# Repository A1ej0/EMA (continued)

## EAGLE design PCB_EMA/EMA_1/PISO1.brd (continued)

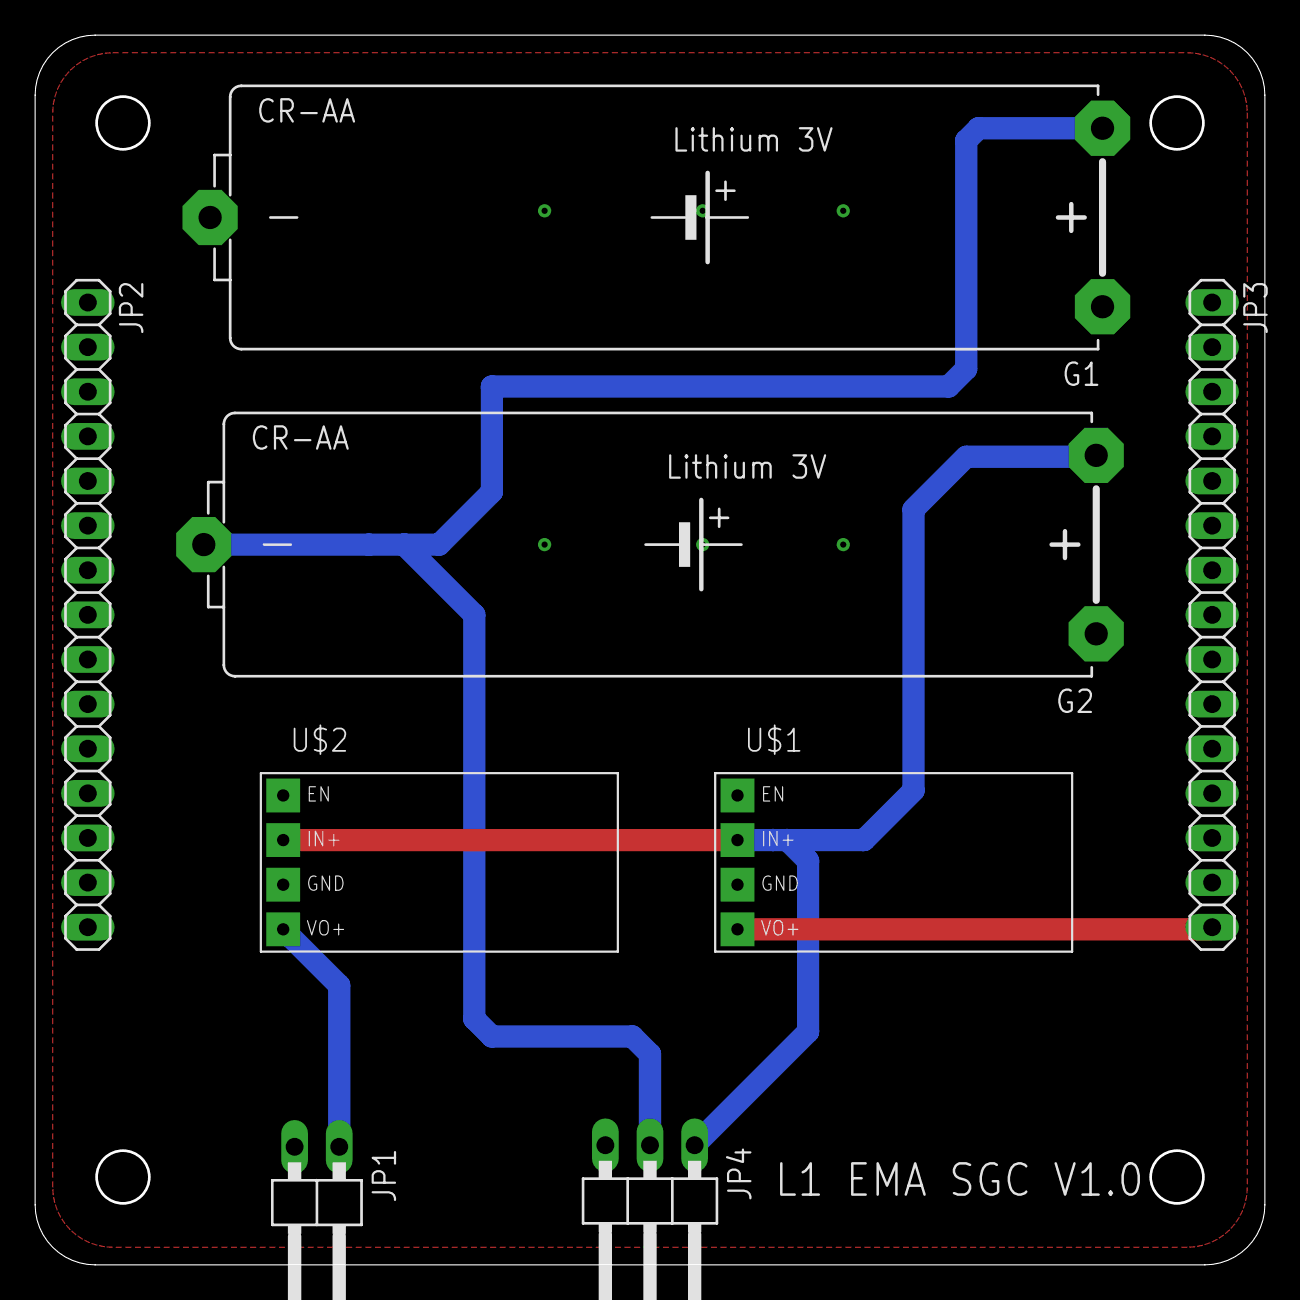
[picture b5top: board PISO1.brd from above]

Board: 2 copper layers, 70.0 x 70.0 mm, 8 parts (0 on the bottom side), 5 nets.

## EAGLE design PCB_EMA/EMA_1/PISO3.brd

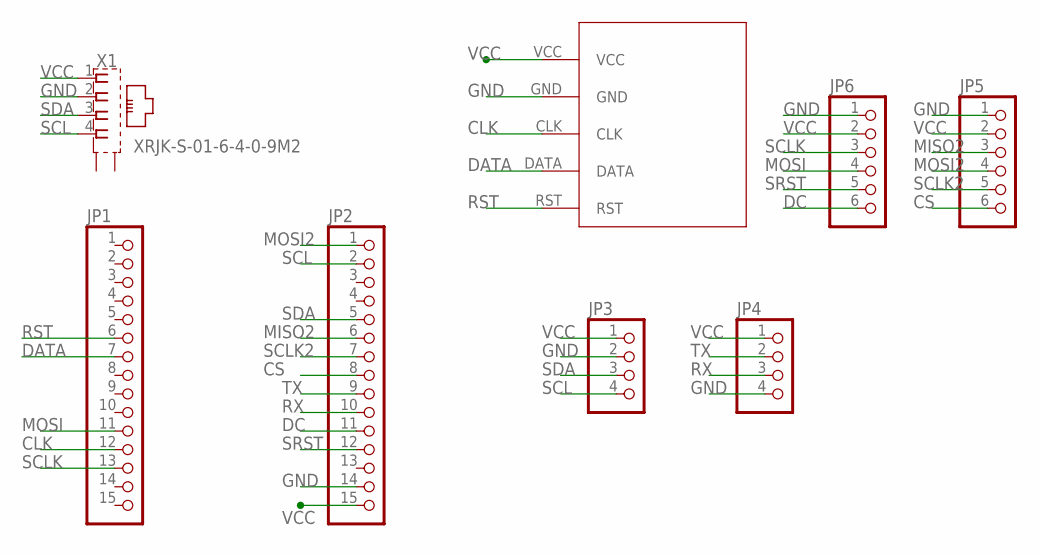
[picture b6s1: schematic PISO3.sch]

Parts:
JP1, JP2: PINHD-1X15; 1X15
JP3, JP4: PINHD-1X4; 1X04
JP5, JP6: PINHD-1X6; 1X06
U$1: DS1302_MODULE; DS1307_MODULE
X1: XRJK-S-01-6-4-0-9M2

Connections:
CLK: JP1.12, U$1.CLK
CS: JP2.8, JP5.6
DATA: JP1.7, U$1.DATA
DC: JP2.11, JP6.6
GND: JP2.14, JP3.2, JP4.4, JP5.1, JP6.1, U$1.GND, X1.2
MISO2: JP2.6, JP5.3
MOSI: JP1.11, JP6.4
MOSI2: JP2.1, JP5.4
RST: JP1.6, U$1.RST
RX: JP2.10, JP4.3
SCL: JP2.2, JP3.4, X1.4
SCLK: JP1.13, JP6.3
SCLK2: JP2.7, JP5.5
SDA: JP2.5, JP3.3, X1.3
SRST: JP2.12, JP6.5
TX: JP2.9, JP4.2
VCC: JP2.15, JP3.1, JP4.1, JP5.2, JP6.2, U$1.VCC, X1.1

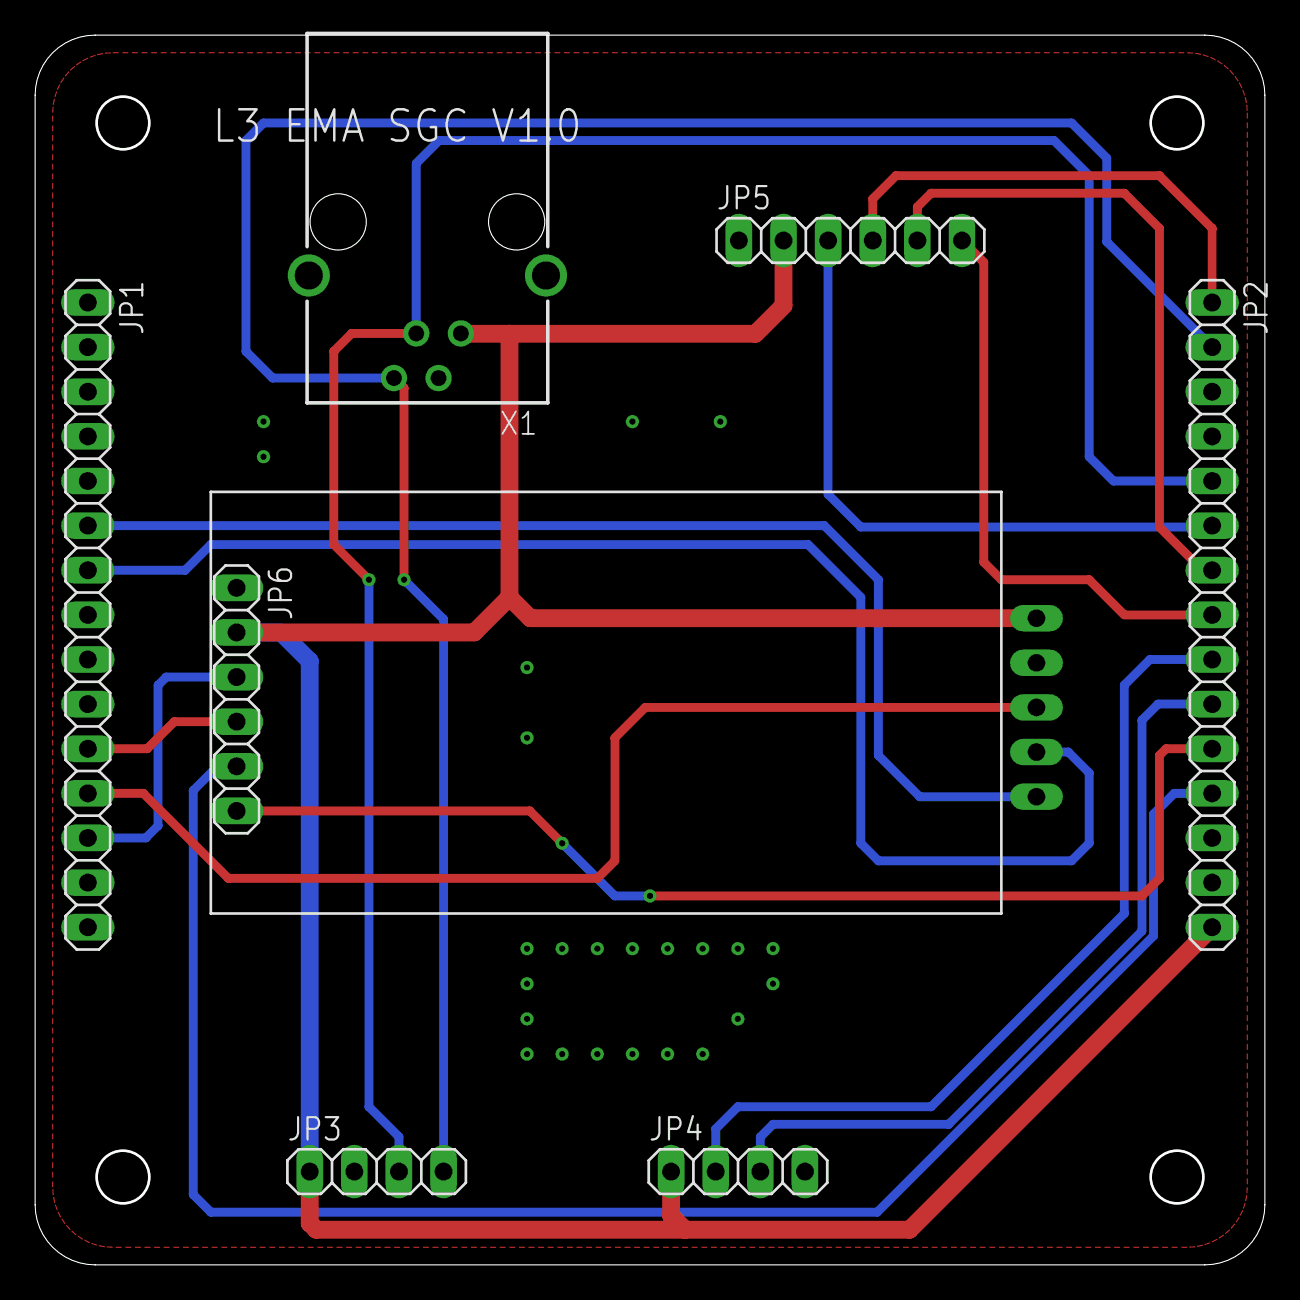
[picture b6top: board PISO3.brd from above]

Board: 2 copper layers, 70.0 x 70.0 mm, 8 parts (1 on the bottom side), 17 nets.

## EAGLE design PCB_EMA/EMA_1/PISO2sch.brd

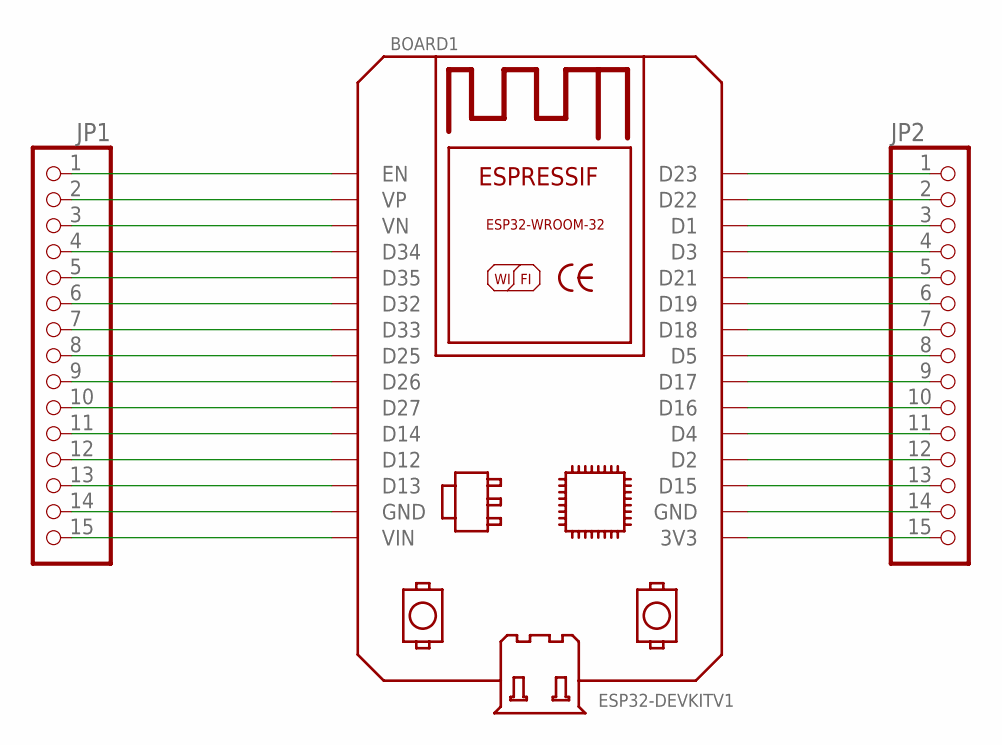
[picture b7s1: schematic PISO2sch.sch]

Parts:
BOARD1: ESP32DEVKITV1; ESP32-DEVKITV1
JP1, JP2: PINHD-1X15; 1X15

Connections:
unnamed: BOARD1.D34, JP1.4
unnamed: BOARD1.VN, JP1.3
unnamed: BOARD1.VP, JP1.2
unnamed: BOARD1.EN, JP1.1
unnamed: BOARD1.D35, JP1.5
unnamed: BOARD1.D32, JP1.6
unnamed: BOARD1.D33, JP1.7
unnamed: BOARD1.D25, JP1.8
unnamed: BOARD1.D26, JP1.9
unnamed: BOARD1.D27, JP1.10
unnamed: BOARD1.D14, JP1.11
unnamed: BOARD1.D12, JP1.12
unnamed: BOARD1.D13, JP1.13
unnamed: BOARD1.GND, JP1.14
unnamed: BOARD1.VIN, JP1.15
unnamed: BOARD1.D23, JP2.1
unnamed: BOARD1.D22, JP2.2
unnamed: BOARD1.D1, JP2.3
unnamed: BOARD1.D3, JP2.4
unnamed: BOARD1.D21, JP2.5
unnamed: BOARD1.D19, JP2.6
unnamed: BOARD1.D18, JP2.7
unnamed: BOARD1.D5, JP2.8
unnamed: BOARD1.D17, JP2.9
unnamed: BOARD1.D16, JP2.10
unnamed: BOARD1.D4, JP2.11
unnamed: BOARD1.D2, JP2.12
unnamed: BOARD1.D15, JP2.13
unnamed: BOARD1.GND@1 (GND), JP2.14
unnamed: BOARD1.3V3, JP2.15

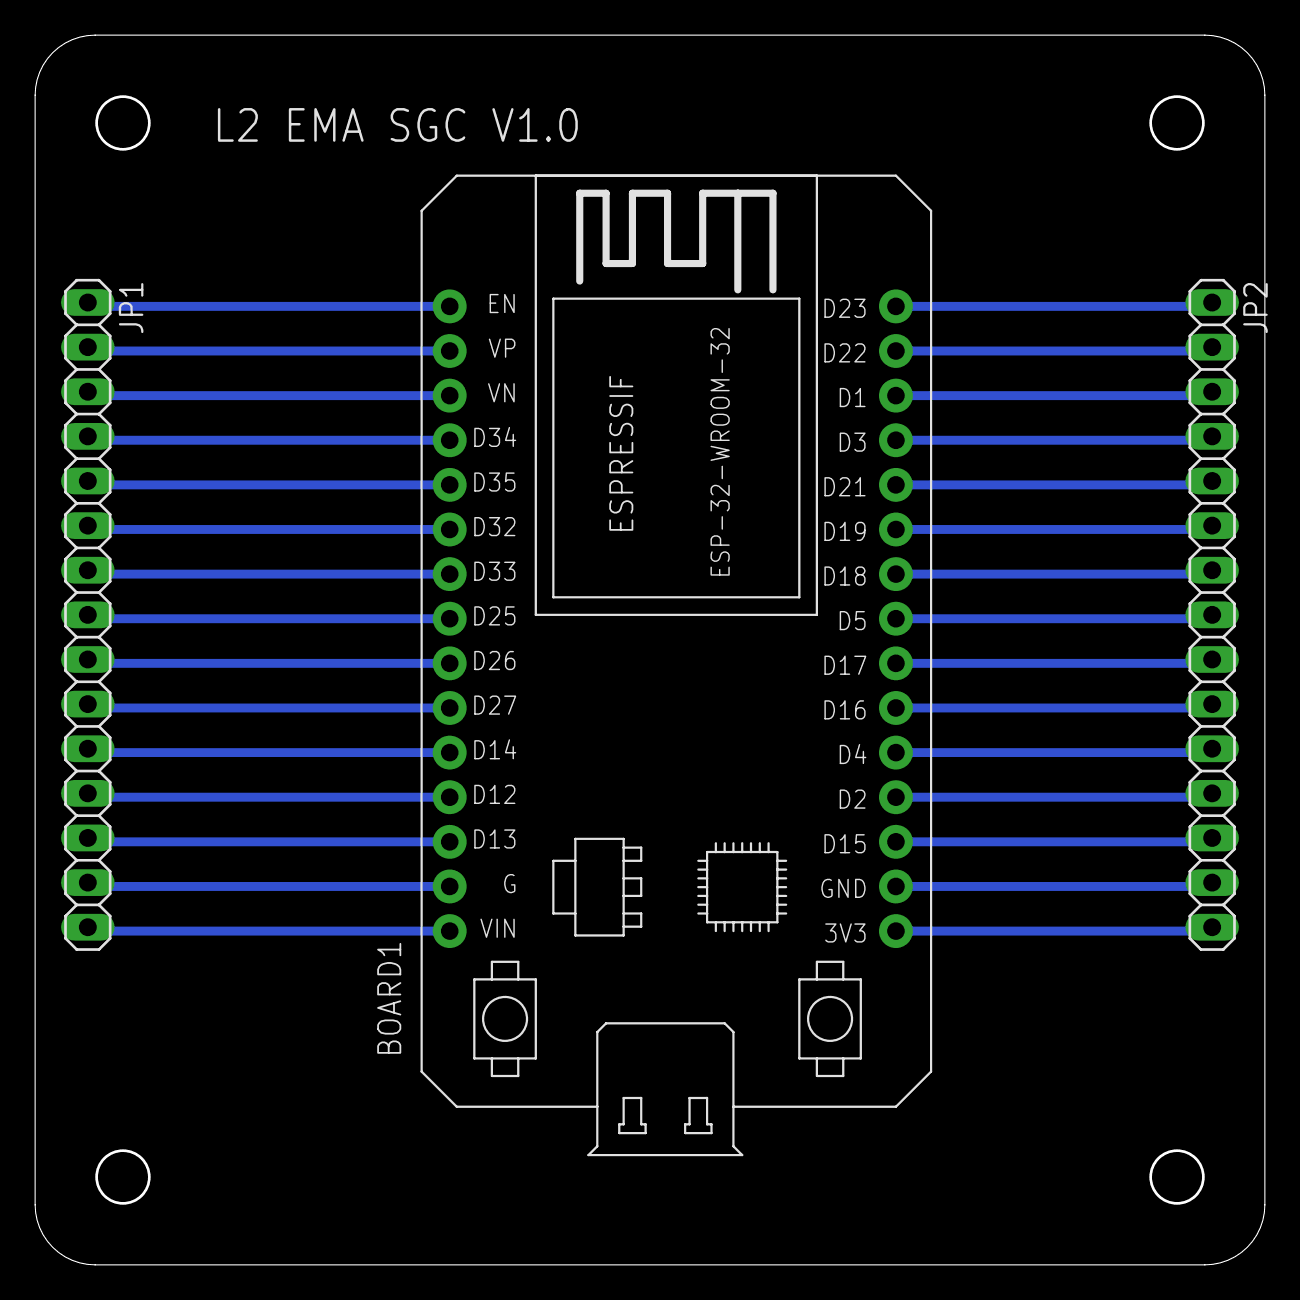
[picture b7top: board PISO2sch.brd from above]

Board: 2 copper layers, 70.0 x 70.0 mm, 3 parts (0 on the bottom side), 30 nets.

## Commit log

2023-02-27 Librerias
2023-02-27 Libreria Global EMA
2023-02-27 Hoja principal del proyecto
2023-03-01 Bluetooth low energy and mpu sensor
2023-03-01 aplicación test BLE y extensión requerida
2023-03-02 EMA_2 updated
2023-03-03 menu local, completo, falta integrar.
2023-03-03 modulo GSM, ajustes y consideraciones iniciales
2023-03-03 menu integrado a EMA, funcionalidad ok
2023-03-03 Etapas del proceso agregadas
2023-03-03 Etapas del proceso UPDATE
2023-03-13 added node-red flows
2023-03-13 corrected node-red flows
2023-03-13 Aplicacion para generar ema.conf
2023-03-13 App para generar conf, version python
2023-03-13 libreria actualizada
    agregado OLED,
    eliminado LCD,
    agregado acelerometro y magnetometro
2023-03-13 Actualizacion menu
    deteccion de sd y archivo de config en la SD
2023-03-13 eliminacion de LCD
    se reemplaza por OLED
2023-03-13 Actualizacion con encoder
2023-03-14 ajustes generales, sensor hall y excepciones
2023-04-10 Create EMA_v20.py
    Libreria optimizada.
2023-04-10 Create main_V2.0.py
    Version optimizada del codigo, control desde archivo local.
2023-04-11 Update EMA_v20.py
    Version revisada, añadido RTC
2023-04-11 Update main_V2.0.py
    Version revisada, añadido RTC
2023-05-13 Esquematico
2023-05-15 PCB design added
2023-05-24 added app bluetooth ver 2
2023-05-26 Create EMA_AlertaGSM.ino
    Modulo GSM de alerta externo
2023-06-06 Actualizacion EMA
    Ultimos avances propuestos
2023-06-06 BLE actualizado
    Actualizacion, para reemplazar valores reales
2023-06-06 ultima version 6 jun
2023-06-13 added app
2023-06-14 Actualizacion EMA
2023-06-15 edited
2023-06-16 app actualizadas
2023-06-16 app actualizada
2023-07-06 Version actualizada 06/07/23
2023-07-06 added mod webrepl
2023-07-07 added wifi download interface
2023-07-11 Ema Sensor Actualizado, correccion bugs
2023-07-11 Sensor Calidad Agua
2023-07-20 app last version
2023-08-18 test2 sim800l MQTT
2023-08-18 sim800l MQTT lib
2023-08-29 flujo para envío de archivo de reporte node-red
2023-08-29 updated app
2023-08-30 updated app and disconnect irq handler
2023-08-30 updated main and EMA library
2023-09-19 app version 19 sept 2023
2023-09-22 Binario sensor conductividad
    para Bluepill, PA_0 = TDS, PA_5=Temperatura.
2023-09-23 librerias sensor conductividad
    para TDS-meter y Termocupla DS1820
2023-10-19 Código flotadores c
2023-11-15 update 15 nov 2023
2023-12-07 Codigo documentado
2023-12-11 limpieza de archivos obsoletos
2023-12-14 Correccion pluviometro
2023-12-15 imagen EMA
2023-12-21 documentación app
2023-12-21 added PCBS and EAGLE filfes
2023-12-26 Actualización flows NodeRed
2023-12-28 update pcb design
2023-12-28 update ema pcb design
2024-03-14 ahorro
2024-04-10 pi pico
2024-04-16 i2c slave
2024-04-22 added PCB eagle files for v4 and sensor board standard
2024-04-26 pdf sensor board
2024-05-06 Create archivo
2024-05-15 Actualizacion EMA LoRa v3
2024-05-15 Actualizacion pi pico
2024-05-20 calidadAgua
2024-05-24 codigo Ahorro
2024-06-05 ultrasonico DF
2024-10-23 Ema APP
2024-10-23 backup node-red
2024-11-20 Ultima version, Noviembre 20204
